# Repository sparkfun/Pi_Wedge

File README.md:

**NOTE:** *This product has been retired from our catalog. For the latest version, check out [BOB-13717](https://www.sparkfun.com/products/13717).*

*If you are looking for more up-to-date info, please check out some of these resources to see how other users are still hacking and improving on this version of the product.*
* *[SparkFun Forum](https://forum.sparkfun.com/)*
* *[Comments Here on GitHub](https://github.com/sparkfun/Pi_Wedge/issues)*
* *[IRC Channel](https://www.sparkfun.com/news/263)*

Pi Wedge - Breakout For Raspberry Pi GPIO Connector
----------------------------

This is the Pi Wedge, a small board that connects to the Raspberry Pi’s 26-pin GPIO connector, and breaks the pins out to breadboard-friendly arrangement and spacing, and even adds a couple of decoupling capacitors on the power supply lines. The “Wedge” also makes the initial bringup process easier - you can plug an FTDI Basic module into the built-in serial port. Each Pi Wedge comes as an easy to assemble kit that can can be inserted into the Raspberry Pi’s GPIO port that allows you to prototype as soon as you are done soldering.

The kit works with both the [Model A](https://www.sparkfun.com/products/11837) and [Model B](https://www.sparkfun.com/products/11546) versions of the Raspberry Pi. 

It adapts the GPIO header on the Pi to a standard solderless breadboard, such as our [meduim](https://www.sparkfun.com/products/12002), [large](https://www.sparkfun.com/products/112) and [extra large](https://www.sparkfun.com/products/12614) breadboards.  While it will technically with with a [mini](https://www.sparkfun.com/products/12043) breadboard, it won't leave much room for external circuitry.

More information can be found on the [Pi Wedge product Page](https://www.sparkfun.com/products/12652), and in the [Pi Wedge hookup guide](https://learn.sparkfun.com/tutorials/236).

This part was created in Eagle v6.5.0.  Software examples were developed using the [WiringPi](wiringpi.com) libraries and utilities.

Repository Contents
-------------------

* **/Hardware** - All Eagle design files (.brd, .sch, .STL)
* **/Software** - C source code for SPI, I2C and GPIO examples.  All use [WiringPi](wiringpi.com) for the underlying device interfaces

Documentation
--------------
* **[Hookup Guide](https://learn.sparkfun.com/tutorials/236)** - Basic hookup guide.

Product Versions
----------------
* [ KIT-12652](https://www.sparkfun.com/products/12652)- Pi Wedge kit

Version History
---------------

* [24dd78154b](https://github.com/sparkfun/Pi_Wedge/commit/9d9670af0e99a6d3599a9afe51451999449d4cf8) PCB revision 1.2 

License Information
-------------------
The hardware is released under [Creative Commons ShareAlike 4.0 International](https://creativecommons.org/licenses/by-sa/4.0/).

The code is beerware; if you see me (or any other SparkFun employee) at the local, and you've found our code helpful, please buy us a round!

Distributed as-is; no warranty is given.

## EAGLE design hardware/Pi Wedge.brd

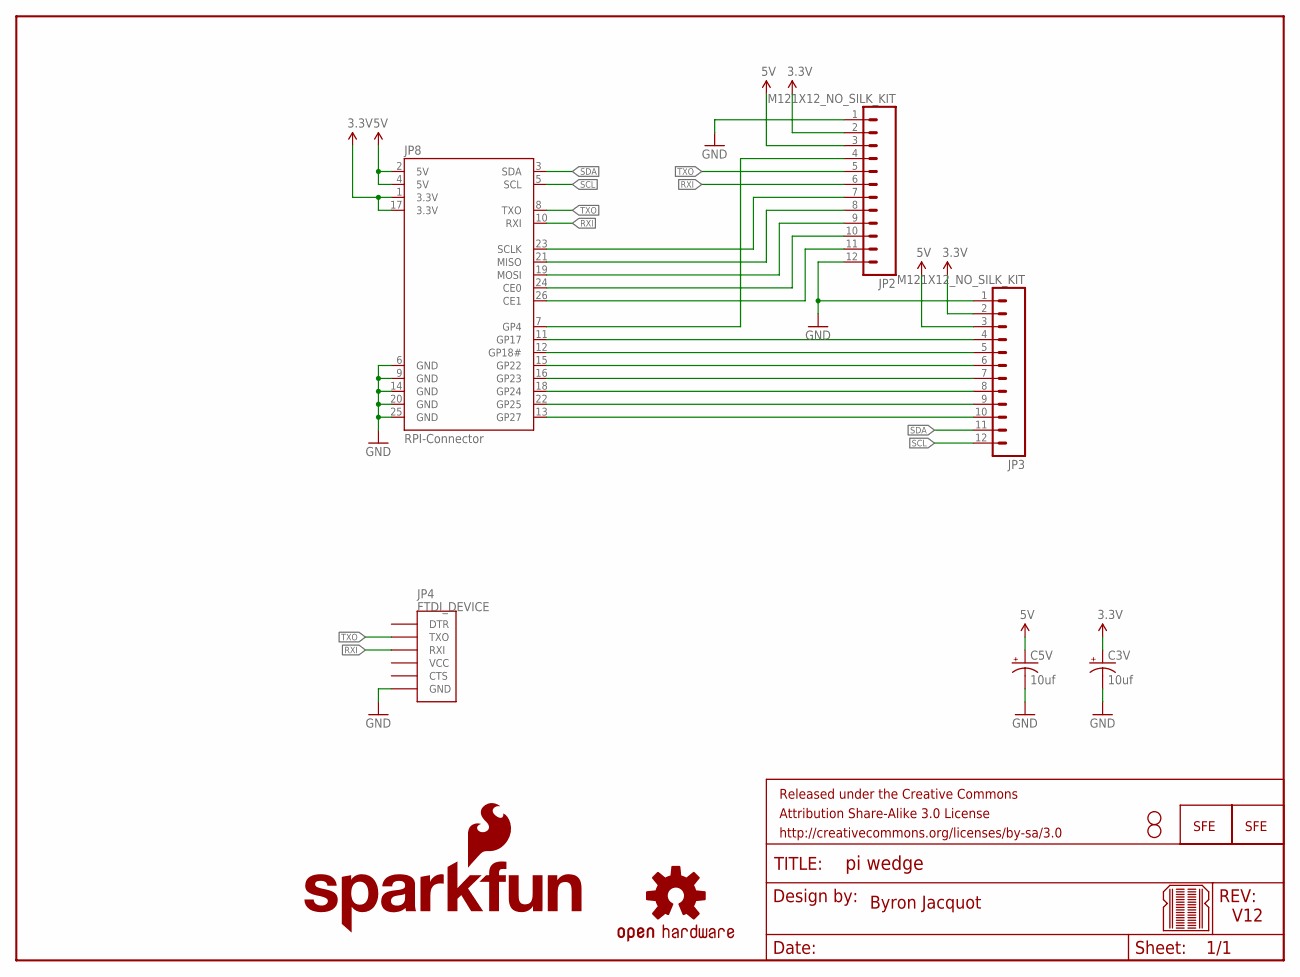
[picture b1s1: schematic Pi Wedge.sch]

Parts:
C3V, C5V: 10uf; CPOL-RADIAL-10UF-25V-KIT
FRAME2: FRAME-LETTER; CREATIVE_COMMONS
JP1, JP5: LOGO-SFESK; SFE-LOGO-FLAME
JP2, JP3: M121X12_NO_SILK_KIT; 1X12_NO_SILK_KIT
JP4: FTDI_DEVICE; FTDI_DEVICE_SIDE
JP8: RPI-Connector; 2X13-SHROUDED
LOGO1: SFE_LOGO_NAME_FLAME.2_INCH; SFE_LOGO_NAME_FLAME_.2
STANDOFF1, STANDOFF2: STAND-OFF
U$1: OSHW-LOGOS; OSHW-LOGO-S
U$2: BREADBOARD_PATTERN; BREADBOARD_SPACING

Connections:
3.3V: C3V.1 (+), JP2.2, JP3.2, JP8.1 (3.3V), JP8.17 (3.3V)
5V: C5V.1 (+), JP2.3, JP3.3, JP8.2 (5V), JP8.4 (5V)
CE0: JP2.10, JP8.24 (CE0)
CE1: JP2.11, JP8.26 (CE1)
GND: C3V.2 (-), C5V.2 (-), JP2.1, JP2.12, JP3.1, JP4.P$6 (GND), JP8.6 (GND), JP8.9 (GND), JP8.14 (GND), JP8.20 (GND), JP8.25 (GND)
GP4: JP2.4, JP8.7 (GP4)
GP17: JP3.4, JP8.11 (GP17)
GP18: JP3.5, JP8.12 (GP18#)
GP22: JP3.6, JP8.15 (GP22)
GP23: JP3.7, JP8.16 (GP23)
GP24: JP3.8, JP8.18 (GP24)
GP25: JP3.9, JP8.22 (GP25)
GP27: JP3.10, JP8.13 (GP27)
MISO: JP2.8, JP8.21 (MISO)
MOSI: JP2.9, JP8.19 (MOSI)
RXI: JP2.6, JP4.P$3 (RXI), JP8.10 (RXI)
SCL: JP3.12, JP8.5 (SCL)
SCLK: JP2.7, JP8.23 (SCLK)
SDA: JP3.11, JP8.3 (SDA)
TXO: JP2.5, JP4.P$2 (TXO), JP8.8 (TXO)

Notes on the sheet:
Byron Jacquot
V12

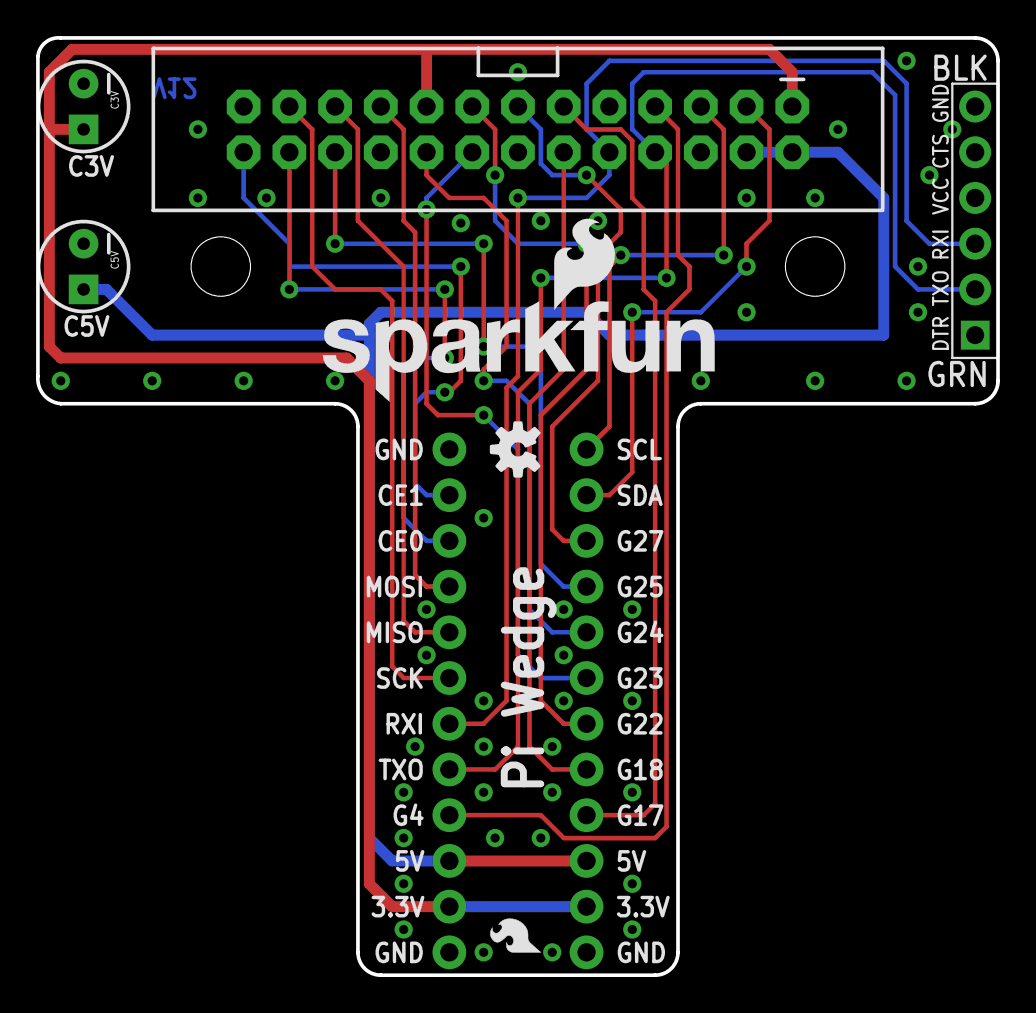
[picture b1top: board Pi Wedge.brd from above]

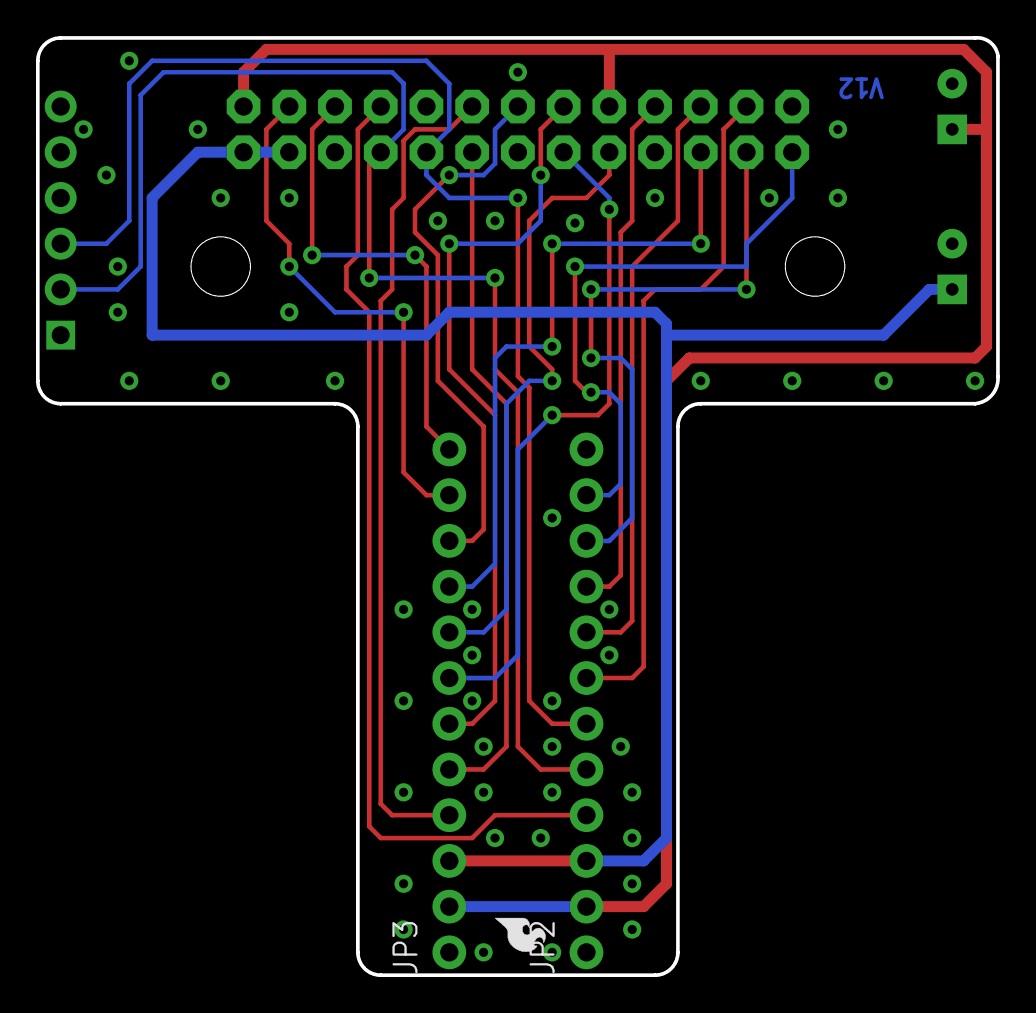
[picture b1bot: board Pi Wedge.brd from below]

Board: 2 copper layers, 53.3 x 52.1 mm, 14 parts (3 on the bottom side), 20 nets.

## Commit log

2013-11-15 Correcting footprint
    The front and back rows needed to be swapped to work with the SparkFun
    23 pin ribbon.
2013-11-20 Adjusting everything.
    Reoriented connectors, added 6-pin FTDI header and extra access to power
    and ground.
2013-11-21 Fixing keepout violations around mtg holes
2013-11-21 Updates based on group review
    Including:
    -Kit footprints for the DIP-spaced headers
    -Wider overall spacing, so power pads match a breadboard more closely
    -PTH decoupling caps on power lines
    -Rounded corners.
    -Vector text
2013-11-21 Touchup to Cap names
2013-12-04 v1.1: Fixing airwire in ground pour.
2013-12-09 Moving vias from under silk.
2014-03-04 V1.2: Design revisions.
    Removing separate 5V and 3.3V connectors.
    Integrating 3.3V and 5V in both sides of the DIP-footprint area.
    Fixing swapped Tx/Rx on FTDI connector.
2014-04-03 Adding software examples
    Using wiringPi to demonstrate C applications that access GPIO, SPI and
    I2C.
2014-04-07 Swapping in new breadboard reference symbol.
    No changes to the board itself.
2014-05-29 Updates before making public.
    README and LICENSE both up to date.
    A few typos in the software were corrected.

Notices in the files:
parts and their libraries:
SparkFun-Connectors: Licensing: CC v3.0 Share-Alike You are welcome to use this library for commercial purposes.
SparkFun-Aesthetics: Released under the Creative Commons Attribution Share-Alike 3.0 License
SparkFun-Aesthetics: http://creativecommons.org/licenses/by-sa/3.0
